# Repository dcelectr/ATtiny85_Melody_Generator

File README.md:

# ATtiny85_Melody_Generator
Based on [Wavetable Melody Generator](http://elm-chan.org/works/mxb/report.html)

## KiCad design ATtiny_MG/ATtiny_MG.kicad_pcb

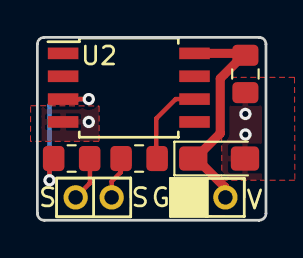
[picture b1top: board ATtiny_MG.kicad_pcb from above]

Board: 2 copper layers, 12.7 x 10.2 mm, 7 parts (0 on the bottom side), 6 nets.

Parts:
C1: 100nF; C_0805_2012Metric_Pad1.18x1.45mm_HandSolder
C2: 100uF; CP_EIA-3216-10_Kemet-I_Pad1.58x1.35mm_HandSolder
J1, J2: Conn_01x02_Male; PinHeader_1x02_P2.00mm_Vertical
R1, R2: 33; R_0805_2012Metric_Pad1.20x1.40mm_HandSolder
U2: ATtiny85-20SU; SOIC-8W_5.3x5.3mm_P1.27mm

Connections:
GND: C1.2, C2.2, J1.2, U2.4
unnamed: J2.1, R1.1
unnamed: J2.2, R2.1
unnamed: R1.2, U2.6
unnamed: R2.2, U2.3
VCC: C1.1, C2.1, J1.1, U2.8

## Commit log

2021-04-01 Initial Upload
2021-04-01 Create firmware
